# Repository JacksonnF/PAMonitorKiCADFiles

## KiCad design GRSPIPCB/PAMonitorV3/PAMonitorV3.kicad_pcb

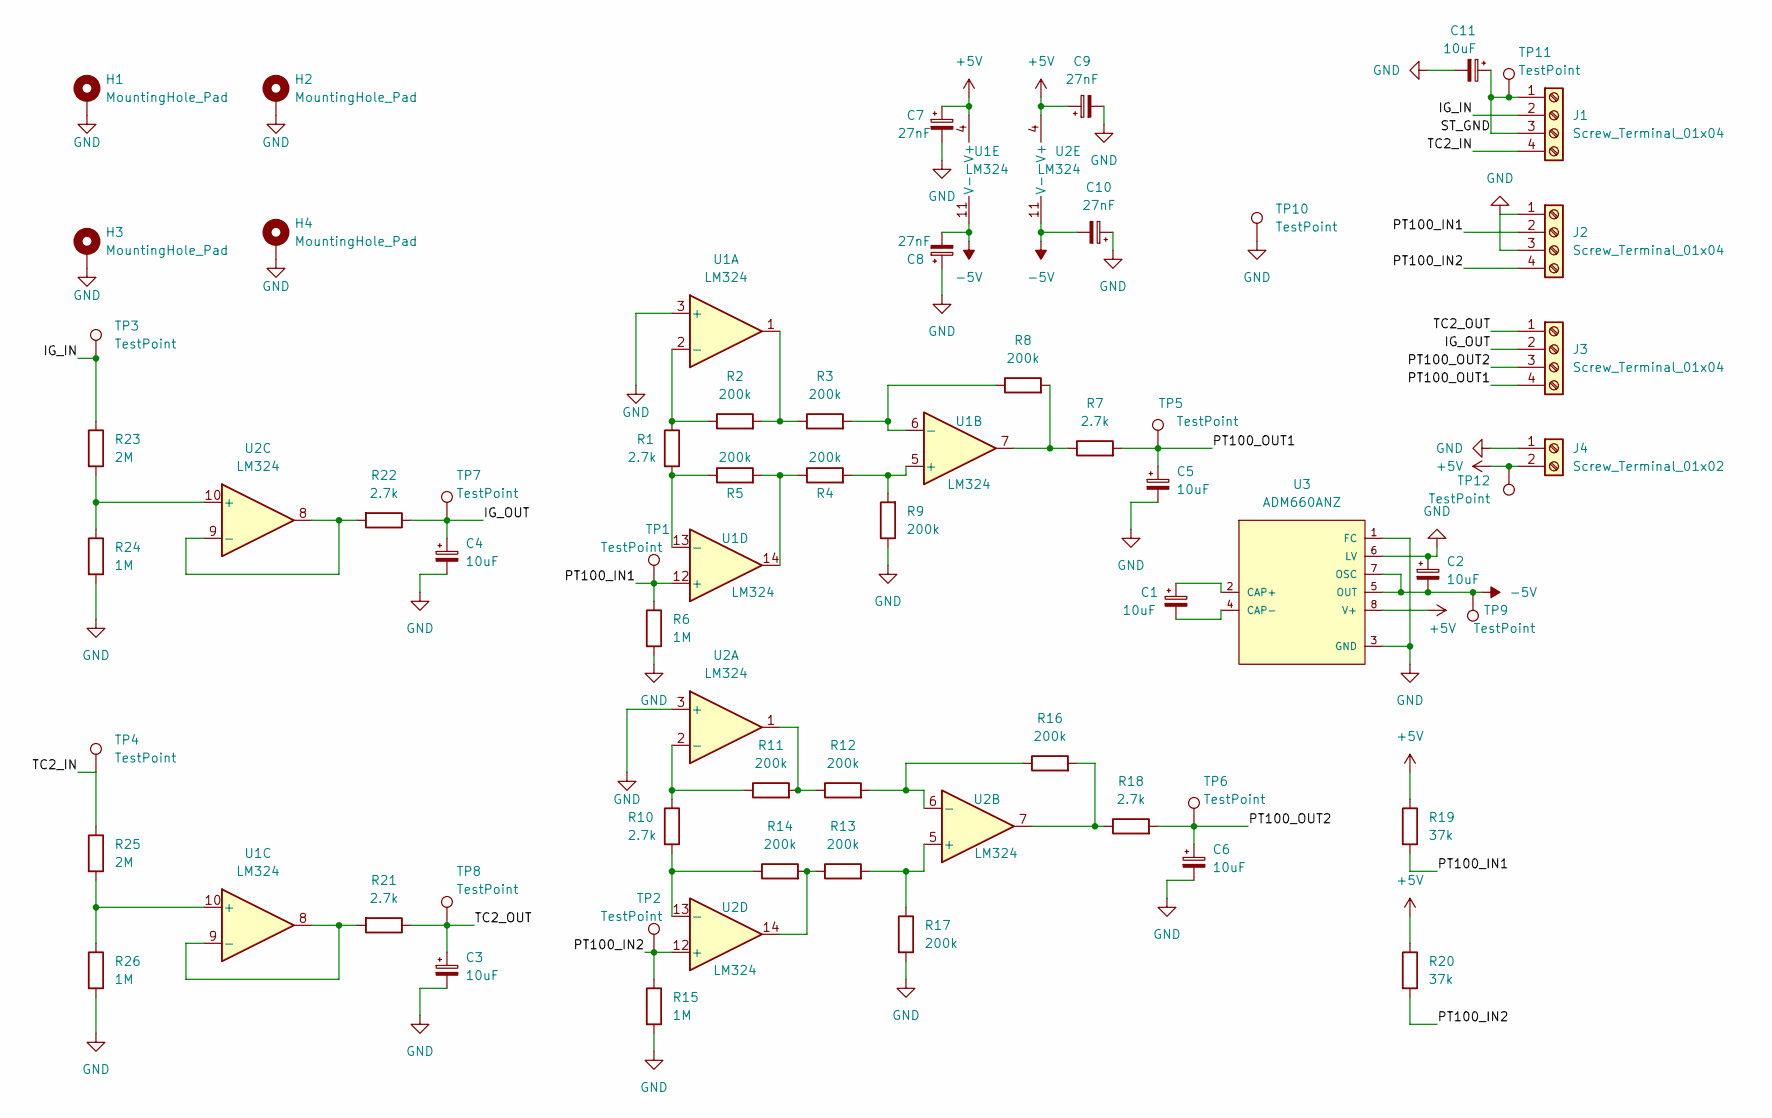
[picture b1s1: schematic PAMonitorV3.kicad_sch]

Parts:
C1, C2, C3, C4, C5, C6, C11: 10uF; CP_Radial_Tantal_D5.5mm_P2.50mm
C7, C8, C9, C10: 27nF; CP_Radial_D5.0mm_P2.50mm
H1, H2, H3, H4: MountingHole_Pad; MountingHole_2.2mm_M2_DIN965_Pad
J1, J2, J3: Screw_Terminal_01x04; TerminalBlock_Phoenix_PT-1,5-4-3.5-H_1x04_P3.50mm_Horizontal
J4: Screw_Terminal_01x02; TerminalBlock_Phoenix_PT-1,5-2-3.5-H_1x02_P3.50mm_Horizontal
R1, R7, R10, R18, R21, R22: 2.7k; R_Axial_DIN0207_L6.3mm_D2.5mm_P10.16mm_Horizontal
R2, R3, R4, R5, R8, R9, R11, R12, R13, R14, R16, R17: 200k; R_Axial_DIN0207_L6.3mm_D2.5mm_P10.16mm_Horizontal
R6, R15, R24, R26: 1M; R_Axial_DIN0207_L6.3mm_D2.5mm_P10.16mm_Horizontal
R19, R20: 37k; R_Axial_DIN0207_L6.3mm_D2.5mm_P10.16mm_Horizontal
R23, R25: 2M; R_Axial_DIN0207_L6.3mm_D2.5mm_P10.16mm_Horizontal
TP1, TP2, TP3, TP4, TP5, TP6, TP7, TP8, TP9, TP10, TP11, TP12: TestPoint; TestPoint_Pad_D1.5mm
U1, U2: LM324; DIP-14_W7.62mm
U3: ADM660ANZ; Analog_Devices_Inc-N-8-0-0-0; mouser part number 584-ADM660ANZ; digikey description IC REG SWTCHD CAP INV RATIO 8DIP

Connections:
+5V: C7.1, C9.1, J4.2, R19.1, R20.1, TP12.1, U1.4 (V+), U2.4 (V+), U3.8 (V+)
-5V: C2.2, C8.2, C10.2, TP9.1, U1.11 (V-), U2.11 (V-), U3.5 (OUT), U3.7 (OSC)
/IG_IN: J1.2, R23.1, TP3.1
/IG_OUT: C4.1, J3.2, R22.1, TP7.1
/PT100_IN1: J2.2, R6.1, R19.2, TP1.1, U1.12 (+)
/PT100_IN2: J2.4, R15.1, R20.2, TP2.1, U2.12 (+)
/PT100_OUT1: C5.1, J3.4, R7.2, TP5.1
/PT100_OUT2: C6.1, J3.3, R18.2, TP6.1
/ST_GND: C11.1, J1.1, J1.3, TP11.1
/TC2_IN: J1.4, R25.1, TP4.1
/TC2_OUT: C3.1, J3.1, R21.1, TP8.1
GND: C2.1, C3.2, C4.2, C5.2, C6.2, C7.2, C8.1, C9.2, C10.1, C11.2, H1.1, H2.1, H3.1, H4.1, J2.1, J2.3, J4.1, R6.2, R9.1, R15.2, R17.2, R24.2, R26.2, TP10.1, U1.3 (+), U2.3 (+), U3.1 (FC), U3.3 (GND), U3.6 (LV)
unnamed: C1.1, U3.2 (CAP+)
unnamed: C1.2, U3.4 (CAP-)
unnamed: R1.1, R2.1, U1.2 (-)
unnamed: R1.2, R5.1, U1.13 (-)
unnamed: R2.2, R3.1, U1.1
unnamed: R3.2, R8.1, U1.6 (-)
unnamed: R4.1, R5.2, U1.14
unnamed: R4.2, R9.2, U1.5 (+)
unnamed: R7.1, R8.2, U1.7
unnamed: R10.1, R11.1, U2.2 (-)
unnamed: R10.2, R14.1, U2.13 (-)
unnamed: R11.2, R12.1, U2.1
unnamed: R12.2, R16.1, U2.6 (-)
unnamed: R13.1, R14.2, U2.14
unnamed: R13.2, R17.1, U2.5 (+)
unnamed: R16.2, R18.1, U2.7
unnamed: R21.2, U1.8, U1.9 (-)
unnamed: R22.2, U2.8, U2.9 (-)
unnamed: R23.2, R24.1, U2.10 (+)
unnamed: R25.2, R26.1, U1.10 (+)

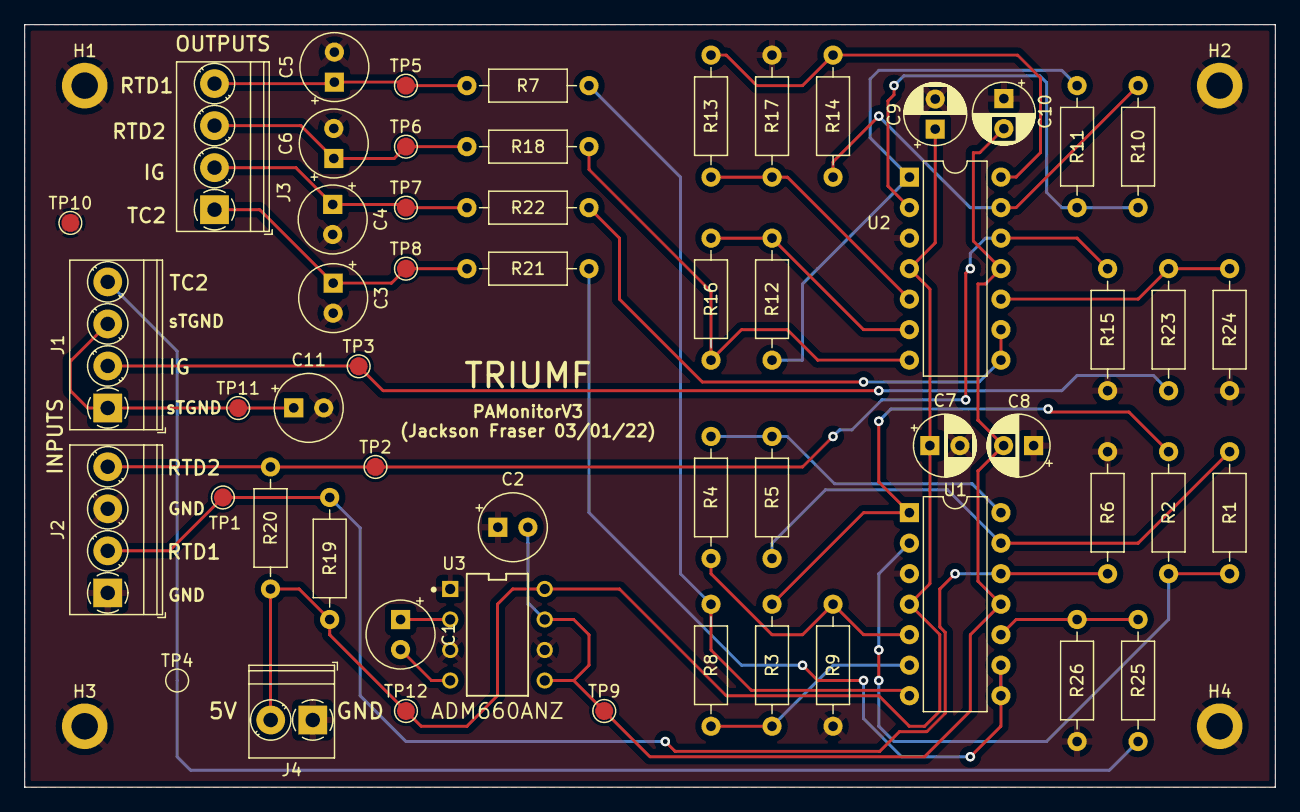
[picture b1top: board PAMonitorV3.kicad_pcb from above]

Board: 2 copper layers, 104.1 x 63.5 mm, 60 parts (0 on the bottom side), 32 nets.
